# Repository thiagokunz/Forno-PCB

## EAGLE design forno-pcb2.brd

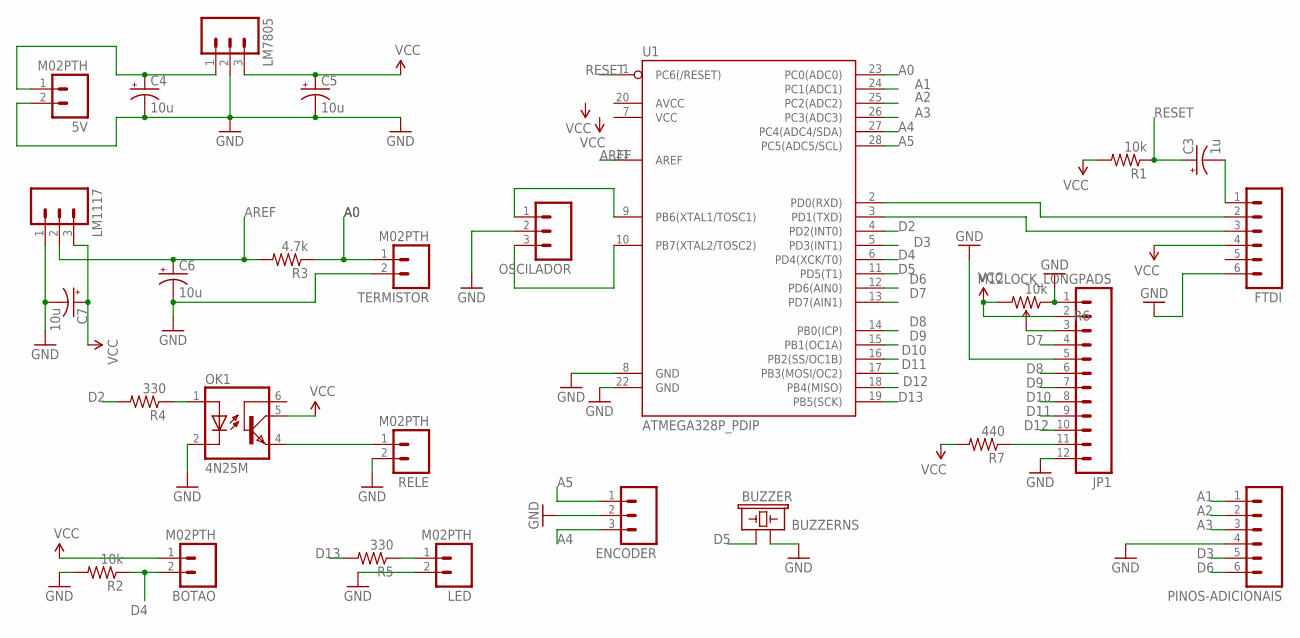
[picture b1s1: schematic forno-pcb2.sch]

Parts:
5V: M02PTH; 1X02
BOTAO: M02PTH; 1X02
BUZZER: BUZZERNS; BUZZER-12MM-NS
C3: 1u; CPOL-RADIAL-10UF-25V
C4, C5, C6, C7: 10u; CPOL-RADIAL-10UF-25V
ENCODER: M03POLAR; MOLEX-1X3
FTDI: M06SIP; 1X06
JP1: M12LOCK_LONGPADS; 1X12_LOCK_LONGPADS
LED: M02PTH; 1X02
LM1117, LM7805: M03POLAR; MOLEX-1X3
OK1: 4N25M; DIL06
OSCILADOR: M03POLAR; MOLEX-1X3
PINOS-ADICIONAIS: M06SIP; 1X06
R1, R2: 10k; 1/6W-RES
R3: 4.7k; 1/6W-RES
R4, R5: 330; 1/6W-RES
R6: 10k; TRIM_POT_PTH
R7: 440; 1/6W-RES
RELE: M02PTH; 1X02
TERMISTOR: M02PTH; 1X02
U1: ATMEGA328P_PDIP; DIL28-3

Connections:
A0: R3.1, TERMISTOR.1, U1.23 (PC0(ADC0))
A1: PINOS-ADICIONAIS.1, U1.24 (PC1(ADC1))
A2: PINOS-ADICIONAIS.2, U1.25 (PC2(ADC2))
A3: PINOS-ADICIONAIS.3, U1.26 (PC3(ADC3))
A4: ENCODER.3, U1.27 (PC4(ADC4/SDA))
A5: ENCODER.1, U1.28 (PC5(ADC5/SCL))
AREF: C6.1 (+), LM1117.2, R3.2, U1.21 (AREF)
D2: R4.2, U1.4 (PD2(INT0))
D3: PINOS-ADICIONAIS.5, U1.5 (PD3(INT1))
D4: BOTAO.2, R2.1, U1.6 (PD4(XCK/T0))
D5: BUZZER.+ (1), U1.11 (PD5(T1))
D6: PINOS-ADICIONAIS.6, U1.12 (PD6(AIN0))
D7: JP1.4, U1.13 (PD7(AIN1))
D8: JP1.6, U1.14 (PB0(ICP))
D9: JP1.7, U1.15 (PB1(OC1A))
D10: JP1.8, U1.16 (PB2(SS/OC1B))
D11: JP1.9, U1.17 (PB3(MOSI/OC2))
D12: JP1.10, U1.18 (PB4(MISO))
D13: R5.2, U1.19 (PB5(SCK))
GND: 5V.2, BUZZER.- (2), C4.2 (-), C5.2 (-), C6.2 (-), C7.2 (-), ENCODER.2, FTDI.6, JP1.1, JP1.5, JP1.12, LED.2, LM1117.1, LM7805.2, OK1.2 (C), OSCILADOR.2, PINOS-ADICIONAIS.4, R2.2, R6.1 (CCW), RELE.2, TERMISTOR.2, U1.8 (GND), U1.22 (GND)
unnamed: FTDI.2, U1.2 (PD0(RXD))
unnamed: FTDI.3, U1.3 (PD1(TXD))
unnamed: C3.2 (-), FTDI.1
unnamed: 5V.1, C4.1 (+), LM7805.1
unnamed: OK1.1 (A), R4.1
unnamed: OK1.4 (EMI), RELE.1
unnamed: OSCILADOR.1, U1.9 (PB6(XTAL1/TOSC1))
unnamed: OSCILADOR.3, U1.10 (PB7(XTAL2/TOSC2))
unnamed: LED.1, R5.1
unnamed: JP1.3, R6.2 (WIPER)
unnamed: JP1.11, R7.1
RESET: C3.1 (+), R1.1, U1.1 (PC6(/RESET))
VCC: BOTAO.1, C5.1 (+), C7.1 (+), FTDI.4, JP1.2, LM1117.3, LM7805.3, OK1.5 (COL), R1.2, R6.3 (CW), R7.2

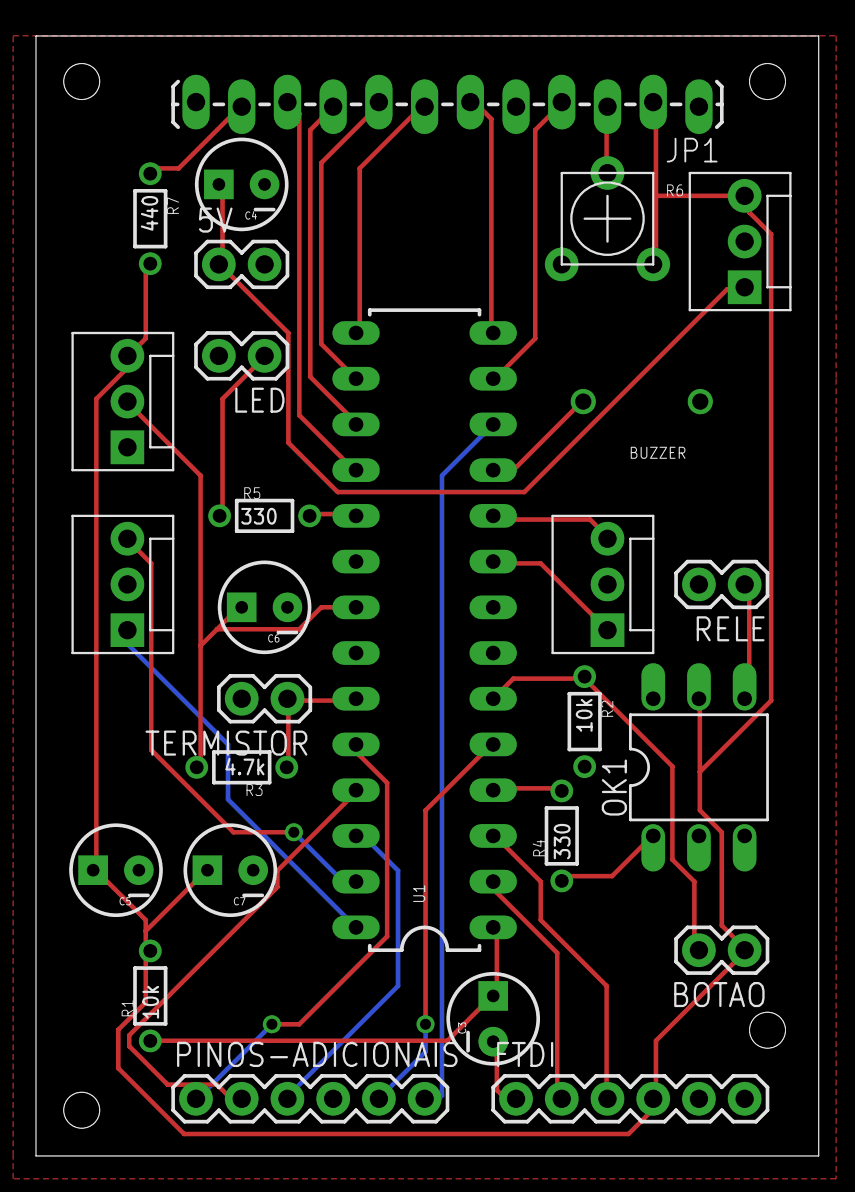
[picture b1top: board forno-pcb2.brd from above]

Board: 2 copper layers, 43.5 x 62.2 mm, 27 parts (0 on the bottom side), 33 nets.

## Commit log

2014-07-22 Forno para solda de componentes SMD
    Este forno é baseado no projeto do Ben Heck. Utiliza um forno elétrico
    como base e um arduino e sensores para controlar a temperatura. Este
    projeto usa o controle de temperatura PID das impressoras 3D RepRap. Um
    relê de estado sólido permite controlar com 5 volts a voltarem
    requerida e corrente necessárias para aquecer o forno.

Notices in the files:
parts and their libraries:
SparkFun-DigitalIC: Licensing: CC v3.0 Share-Alike You are welcome to use this library for commercial purposes.
